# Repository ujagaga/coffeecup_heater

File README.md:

# coffeecup_heater
Keeps coffee hot indefinitely

Here is firmware for a coffee cup heater with a thermostat to hold coffee cup temperature high. 
It uses Digistump module with AtTiny85 to measure temperature via DS18B20 and start heater comprized of 220 ohm resistors.
LEDs are connected via resistors directly to the heater so they light up when the heater is on. 
I have modified the digistump module a bit, removed the 5V stabilizer and added an N channel mosfet to start the heater.
A microswitch is used to detect when you place a cup on the device. 
The Digistump module is placed under the heater and powered from a 5V/2A Phone charger. 
You can use PB2 to connect a UART and read current temperature.

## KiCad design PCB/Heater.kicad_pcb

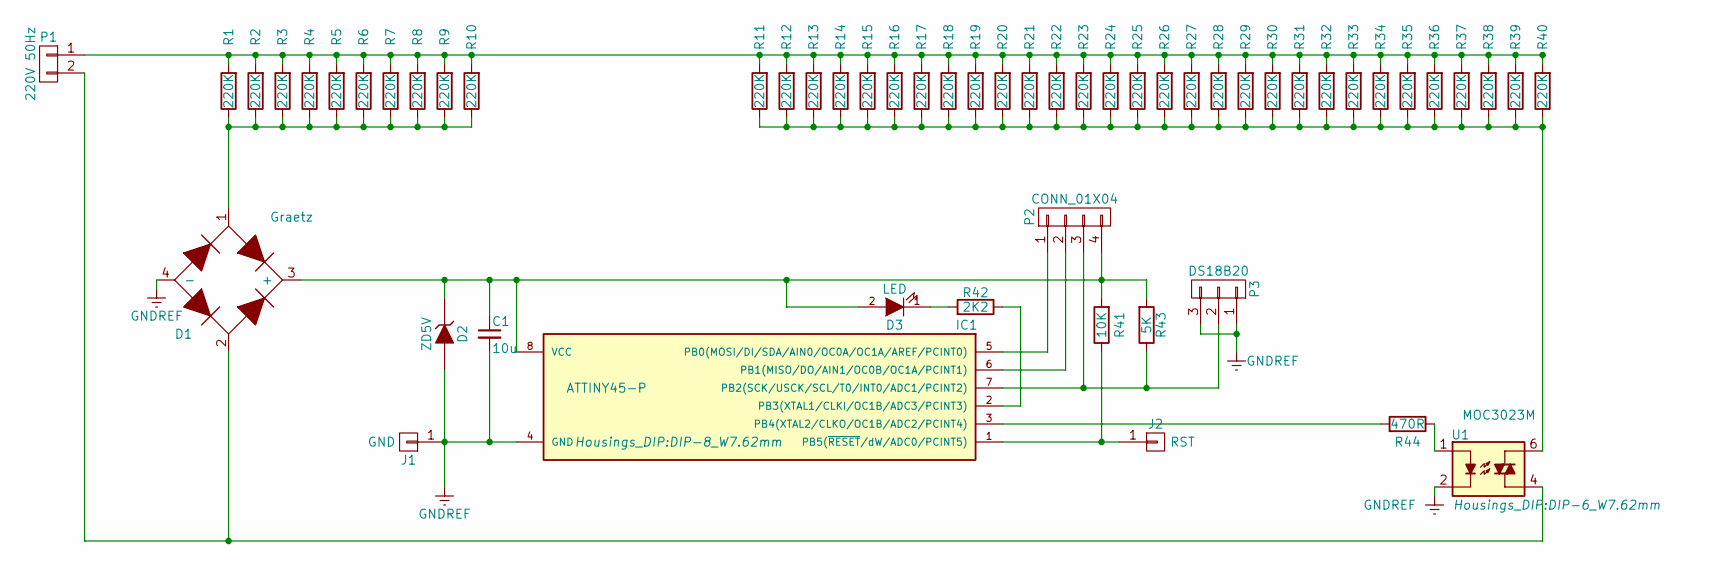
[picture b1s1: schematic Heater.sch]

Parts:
C1: 10u; C_0805_HandSoldering
D1: Graetz; DIP-6_W7.62mm
D2: ZD5V; D_MELF_Handsoldering
D3: LED; Socket_Strip_Straight_1x02_Pitch2.54mm
IC1: ATTINY45-P; DIP-8_W7.62mm
J1: GND; Pin_Header_Straight_1x01_Pitch1.27mm
J2: RST; Pin_Header_Straight_1x01_Pitch1.27mm
P1: 220V 50Hz; Socket_Strip_Angled_1x02_Pitch2.54mm
P2: CONN_01X04; Pin_Header_Straight_1x04_Pitch2.54mm
P3: DS18B20; TO-92_Inline_Wide
R1, R2, R3, R4, R5, R6, R7, R8, R9, R10, R11, R12, R13, R14, R15, R16, R17, R18, R19, R20, R21, R22, R23, R24, R25, R26, R27, R28, R29, R30, R31, R32, R33, R34, R35, R36, R37, R38, R39, R40: 220K; R_1210
R41: 10K; R_0805
R42: 2K2; R_0805
R43: 5K; R_0805
R44: 470R; R_0805
U1: MOC3023M; DIP-6_W7.62mm

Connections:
GNDREF: C1.2, D1.4 (-), D2.2 (A), IC1.4 (GND), J1.1, P3.1, P3.3, U1.2
unnamed: C1.1, D1.3 (+), D2.1 (K), D3.2 (A), IC1.8 (VCC), P2.4, R41.2, R43.2
unnamed: D1.1, R1.1, R2.1, R3.1, R4.1, R5.1, R6.1, R7.1, R8.1, R9.1, R10.1
unnamed: D1.2, P1.2, U1.4
unnamed: D3.1 (K), R42.2
unnamed: IC1.1 (PB5(~RESET~/dW/ADC0/PCINT5)), J2.1, R41.1
unnamed: IC1.2 (PB3(XTAL1/CLKI/OC1B/ADC3/PCINT3)), R42.1
unnamed: IC1.3 (PB4(XTAL2/CLKO/OC1B/ADC2/PCINT4)), R44.2
unnamed: IC1.5 (PB0(MOSI/DI/SDA/AIN0/OC0A/OC1A/AREF/PCI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), P2.1
unnamed: IC1.6 (PB1(MISO/DO/AIN1/OC0B/OC1A/PCINT1)), P2.2
unnamed: IC1.7 (PB2(SCK/USCK/SCL/T0/INT0/ADC1/PCINT2)), P2.3, P3.2, R43.1
unnamed: P1.1, R1.2, R2.2, R3.2, R4.2, R5.2, R6.2, R7.2, R8.2, R9.2, R10.2, R11.2, R12.2, R13.2, R14.2, R15.2, R16.2, R17.2, R18.2, R19.2, R20.2, R21.2, R22.2, R23.2, R24.2, R25.2, R26.2, R27.2, R28.2, R29.2, R30.2, R31.2, R32.2, R33.2, R34.2, R35.2, R36.2, R37.2, R38.2, R39.2, R40.2
unnamed: R11.1, R12.1, R13.1, R14.1, R15.1, R16.1, R17.1, R18.1, R19.1, R20.1, R21.1, R22.1, R23.1, R24.1, R25.1, R26.1, R27.1, R28.1, R29.1, R30.1, R31.1, R32.1, R33.1, R34.1, R35.1, R36.1, R37.1, R38.1, R39.1, R40.1, U1.6
unnamed: R44.1, U1.1

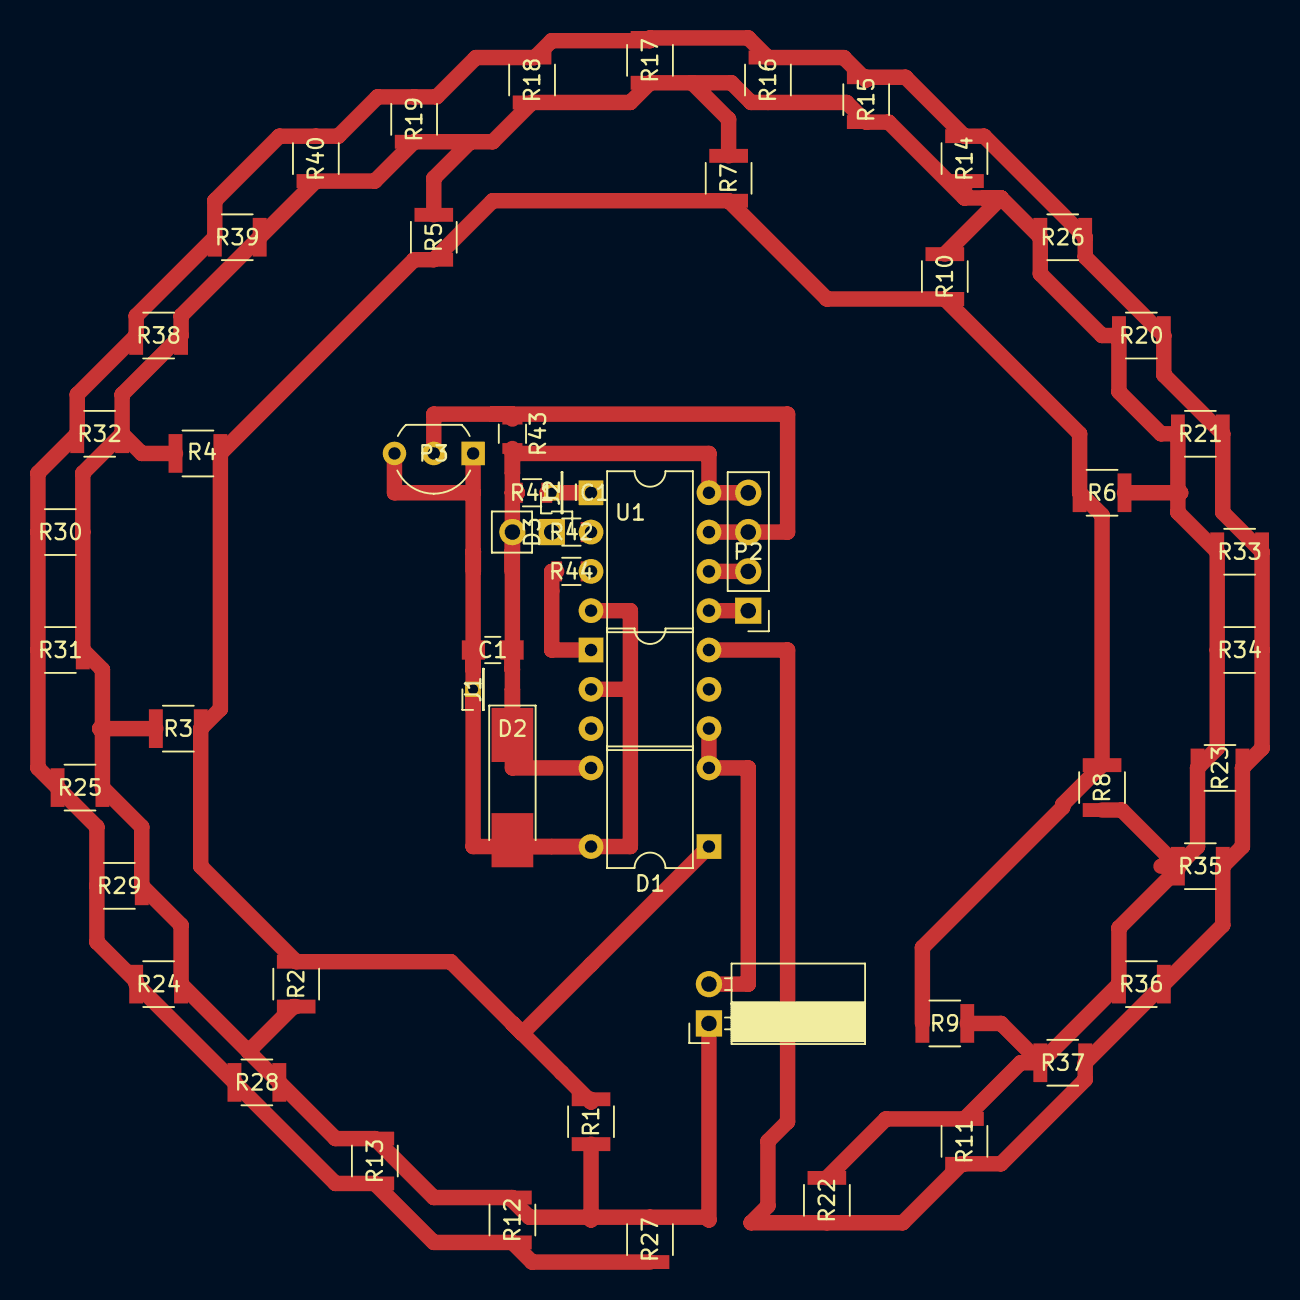
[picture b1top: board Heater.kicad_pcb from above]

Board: 2 copper layers, 55 parts (0 on the bottom side), 14 nets.

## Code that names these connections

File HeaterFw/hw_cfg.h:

/*
 * hw_cfg.h
 *
 *  Created on: Nov 23, 2017
 *      Author: rada
 */

#ifndef HW_CFG_H_
#define HW_CFG_H_

#define DS_COMM_PIN			(PB0)
#define HEATER_PIN			(PB1)
#define SW_PIN				(PB3)

#define DBG_UART_TX_PIN		(PB2)

#define DBG_UART_ENABLE		(1)
#define DBG_UART_BAUDRATE	(9600)


#endif /* HW_CFG_H_ */

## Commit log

2017-07-08 First PCB with thyristor
2017-07-08 Updated Schematic and PCB to use optotriac
2017-07-10 Added fw
2017-07-10 Not working yet
2017-07-10 Not working
2017-07-11 finished working version of the PCB and FW
2017-07-11 A better packed version
2017-07-12 new design with stronger resistors
2017-07-13 Possible layout
2017-11-22 New idea with AtTiny85
2017-11-27 Added sensing on new board
2017-12-06 Changed for 3 wire config
2017-12-08 first working version
2017-12-08 Final version
2017-12-10 Finished the version 1 description with a picture
2017-12-10 Finished version1 with schematic
2017-12-10 Version 2
2017-12-15 Finished
2018-02-02 Added UART debug
